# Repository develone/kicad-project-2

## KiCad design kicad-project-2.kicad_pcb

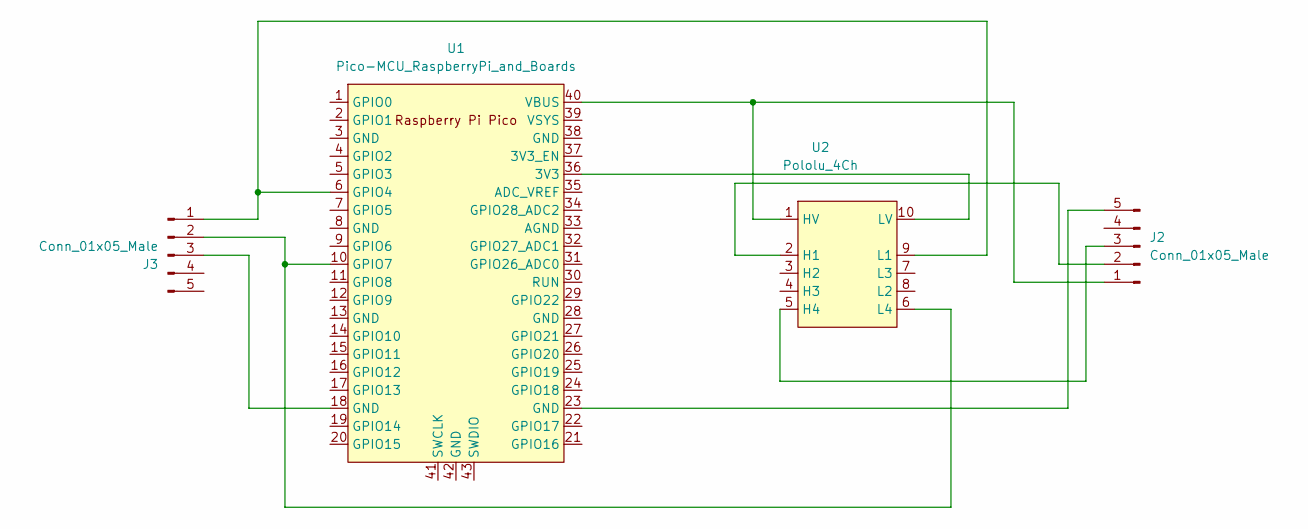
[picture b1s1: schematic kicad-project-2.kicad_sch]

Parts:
J2, J3: Conn_01x05_Male; PinSocket_1x05_P1.00mm_Vertical
U1: Pico-MCU_RaspberryPi_and_Boards; DIP-40_W25.4mm_Socket_LongPads
U2: Pololu_4Ch; DIP-10_W7.62mm

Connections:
unnamed: J2.1, U1.40 (VBUS), U2.1 (HV)
unnamed: J2.2, U2.2 (H1)
unnamed: J2.3, U2.5 (H4)
unnamed: J2.5, U1.23 (GND)
unnamed: J3.3, U1.18 (GND)
unnamed: J3.1, U1.6 (GPIO4), U2.9 (L1)
unnamed: J3.2, U1.10 (GPIO7), U2.6 (L4)
unnamed: U1.36 (3V3), U2.10 (LV)

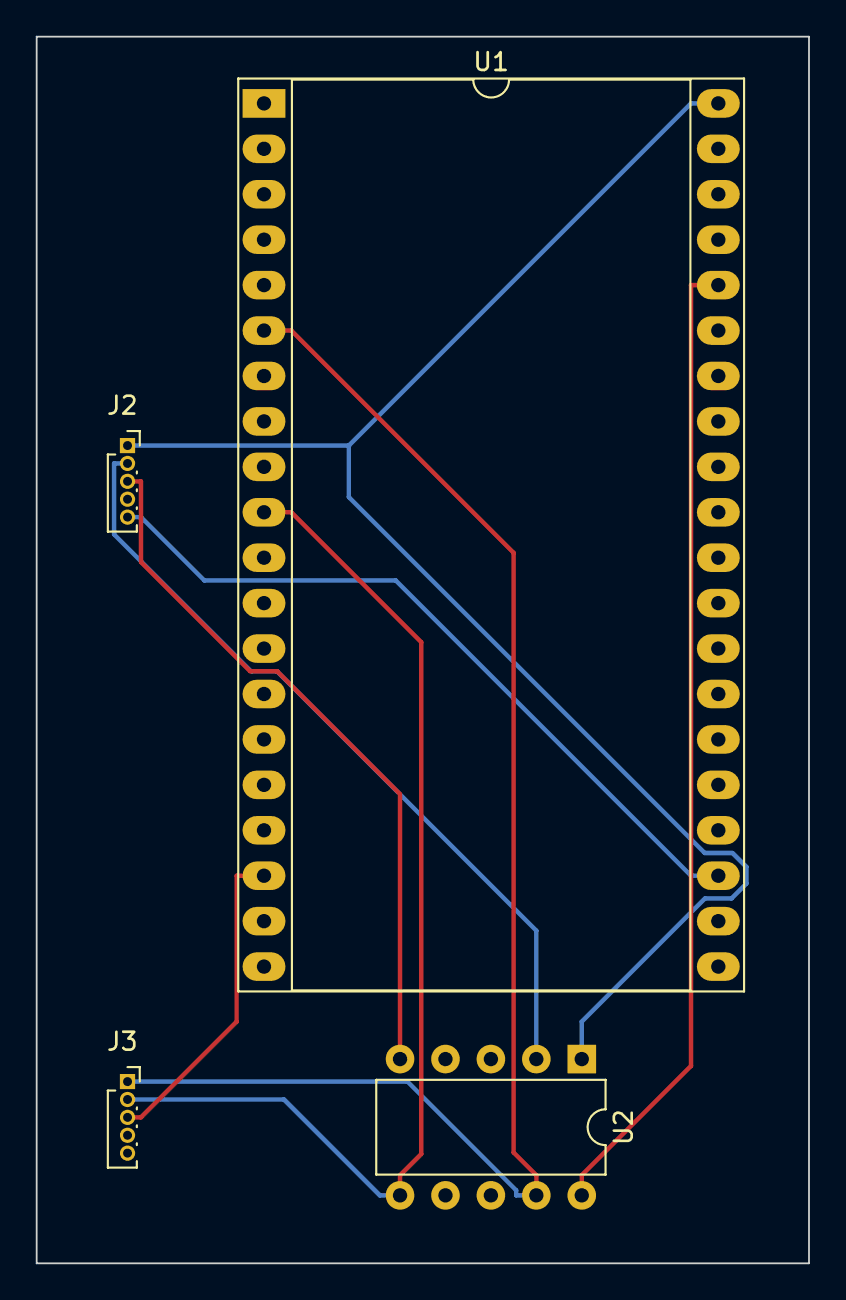
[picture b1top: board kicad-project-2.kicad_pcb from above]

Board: 2 copper layers, 43.2 x 68.6 mm, 4 parts (0 on the bottom side), 8 nets.

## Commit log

2024-04-24 initial files.
2024-04-24 pass 1
2024-04-24 missing from previous commit
